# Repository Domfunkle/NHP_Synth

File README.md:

# NHP_Synth: ESP32 Dual DDS Synthesizer

This project implements a dual-channel Direct Digital Synthesis (DDS) signal generator on the ESP32 platform. It features:

- Two independent sine wave outputs (via DACs on GPIO25 and GPIO26)
- Precise square wave output (GPIO18) synchronized to DDS phase
- UART command interface for real-time control
- Phase, frequency, and amplitude control for each channel
- Odd harmonic mixing with amplitude and phase control per channel (total 8 simultaneous harmonics across both channels)
- External sync input (GPIO19, rising edge)
- High-resolution timer for accurate waveform generation

## Features
- **Frequency Range:** 20 Hz to 8 kHz (configurable)
- **Amplitude Ramping:** Smooth amplitude changes to prevent clicks
- **Phase Control:** Set phase offset for each channel
- **Harmonic Mixing:** Add odd harmonics (3rd, 5th, 7th, etc) to either channel, with amplitude and phase control. Up to a total of 8 harmonics can be active across both channels at once.
- **UART Commands:**
  - `wf[a|b]<freq>`: Set channel A or B frequency (Hz)
  - `wp[a|b]<deg>`: Set channel A or B phase (degrees, -180 to +180)
  - `wa[a|b]<ampl>`: Set channel A or B amplitude (0-100)
  - `wh[a|b]<order>,<pct>[,<phase>]`: Mix odd harmonic to channel A or B (e.g. `wha3,10` for 10% 3rd harmonic, or `wha7,20,-90` for 20% 7th harmonic at -90° phase)
  - `whcl[a|b]`: Clear all harmonics for channel A or B
  - `help`: Show help message

## Hardware Connections
- **DAC Channel A:** GPIO25
- **DAC Channel B:** GPIO26
- **Square Wave Output:** GPIO18
- **Sync Input:** GPIO19 (rising edge, with pulldown)

## Project Structure

```
NHP_Synth/
├── firmware/           # ESP32 firmware (ESP-IDF project)
│   ├── main/          # Main application source
│   ├── .devcontainer/ # ESP-IDF development container
│   └── .vscode/       # ESP32-specific VS Code settings
├── host/              # Python host control interface
│   ├── synth_control/ # Python control library
│   ├── examples/      # Usage examples
│   ├── .devcontainer/ # Python development container
│   └── .vscode/       # Python-specific VS Code settings
├── tools/             # Shared utilities and scripts
└── .vscode/           # Root workspace configuration
```

## Build & Flash

### Firmware (ESP32)
Navigate to the firmware directory and use ESP-IDF:

```bash
cd firmware
idf.py build
idf.py -p /dev/ttyUSB0 flash
```

Or use the convenient script for multiple devices:

```bash
./tools/flash_multiple.sh
```

## Host Control (Python)

A Python interface is provided for programmatic control:

```bash
cd host
python3 -m venv .venv
source .venv/bin/activate
pip install -r requirements.txt

# Run examples
python examples/basic_control.py
python examples/harmonic_sweep.py
```

## UART Usage
Connect to the ESP32 UART (default 115200 baud) and type commands as described above. Type `help` for a list of commands.

## Linux commands to test UART
```bash
# Generate a square wave on Channel A at 50Hz
printf "wha3,33\r" > /dev/ttyUSB1
printf "wha5,20\r" > /dev/ttyUSB1
printf "wha7,14\r" > /dev/ttyUSB1
printf "wha9,11\r" > /dev/ttyUSB1
printf "wha11,9\r" > /dev/ttyUSB1
printf "wha13,8\r" > /dev/ttyUSB1
printf "wha15,7\r" > /dev/ttyUSB1
printf "wha17,6\r" > /dev/ttyUSB1
```

```bash
# Clear all harmonics for Channel A and B
printf "whcla\r" > /dev/ttyUSB1
printf "whclb\r" > /dev/ttyUSB1
```

```bash
# Rolling harmonic phase for Channel A and B
ph=-180
while true; do
    printf "wha5,20,%d\n" "$ph" > /dev/ttyUSB1
    invph=$((ph * -1))
    printf "whb3,10,%d\n" "$invph" > /dev/ttyUSB1
    sleep 0.03
    ph=$((ph + 1))
    if [ "$ph" -gt 180 ]; then
        ph=-180
    fi
done
```

## Development

### VS Code Workspace
Open the multi-root workspace for unified development:
```bash
code .vscode/NHP_Synth.code-workspace
```

### DevContainers
Each component has its own development container:
- **Firmware**: ESP-IDF container with all tools
- **Host**: Python container with analysis libraries

### Tools
- `tools/flash_multiple.sh` - Flash firmware to multiple devices
- `tools/uart_test.py` - Test UART communication

## File Structure
- `firmware/main/main.c`: Main ESP32 application source
- `firmware/build/`: Build artifacts (ignored by git)
- `host/synth_control/`: Python control library
- `host/examples/`: Python usage examples
- `tools/`: Shared utilities and scripts
- `.gitignore`: Excludes build and config files from version control

## License
MIT License (or specify your license here)

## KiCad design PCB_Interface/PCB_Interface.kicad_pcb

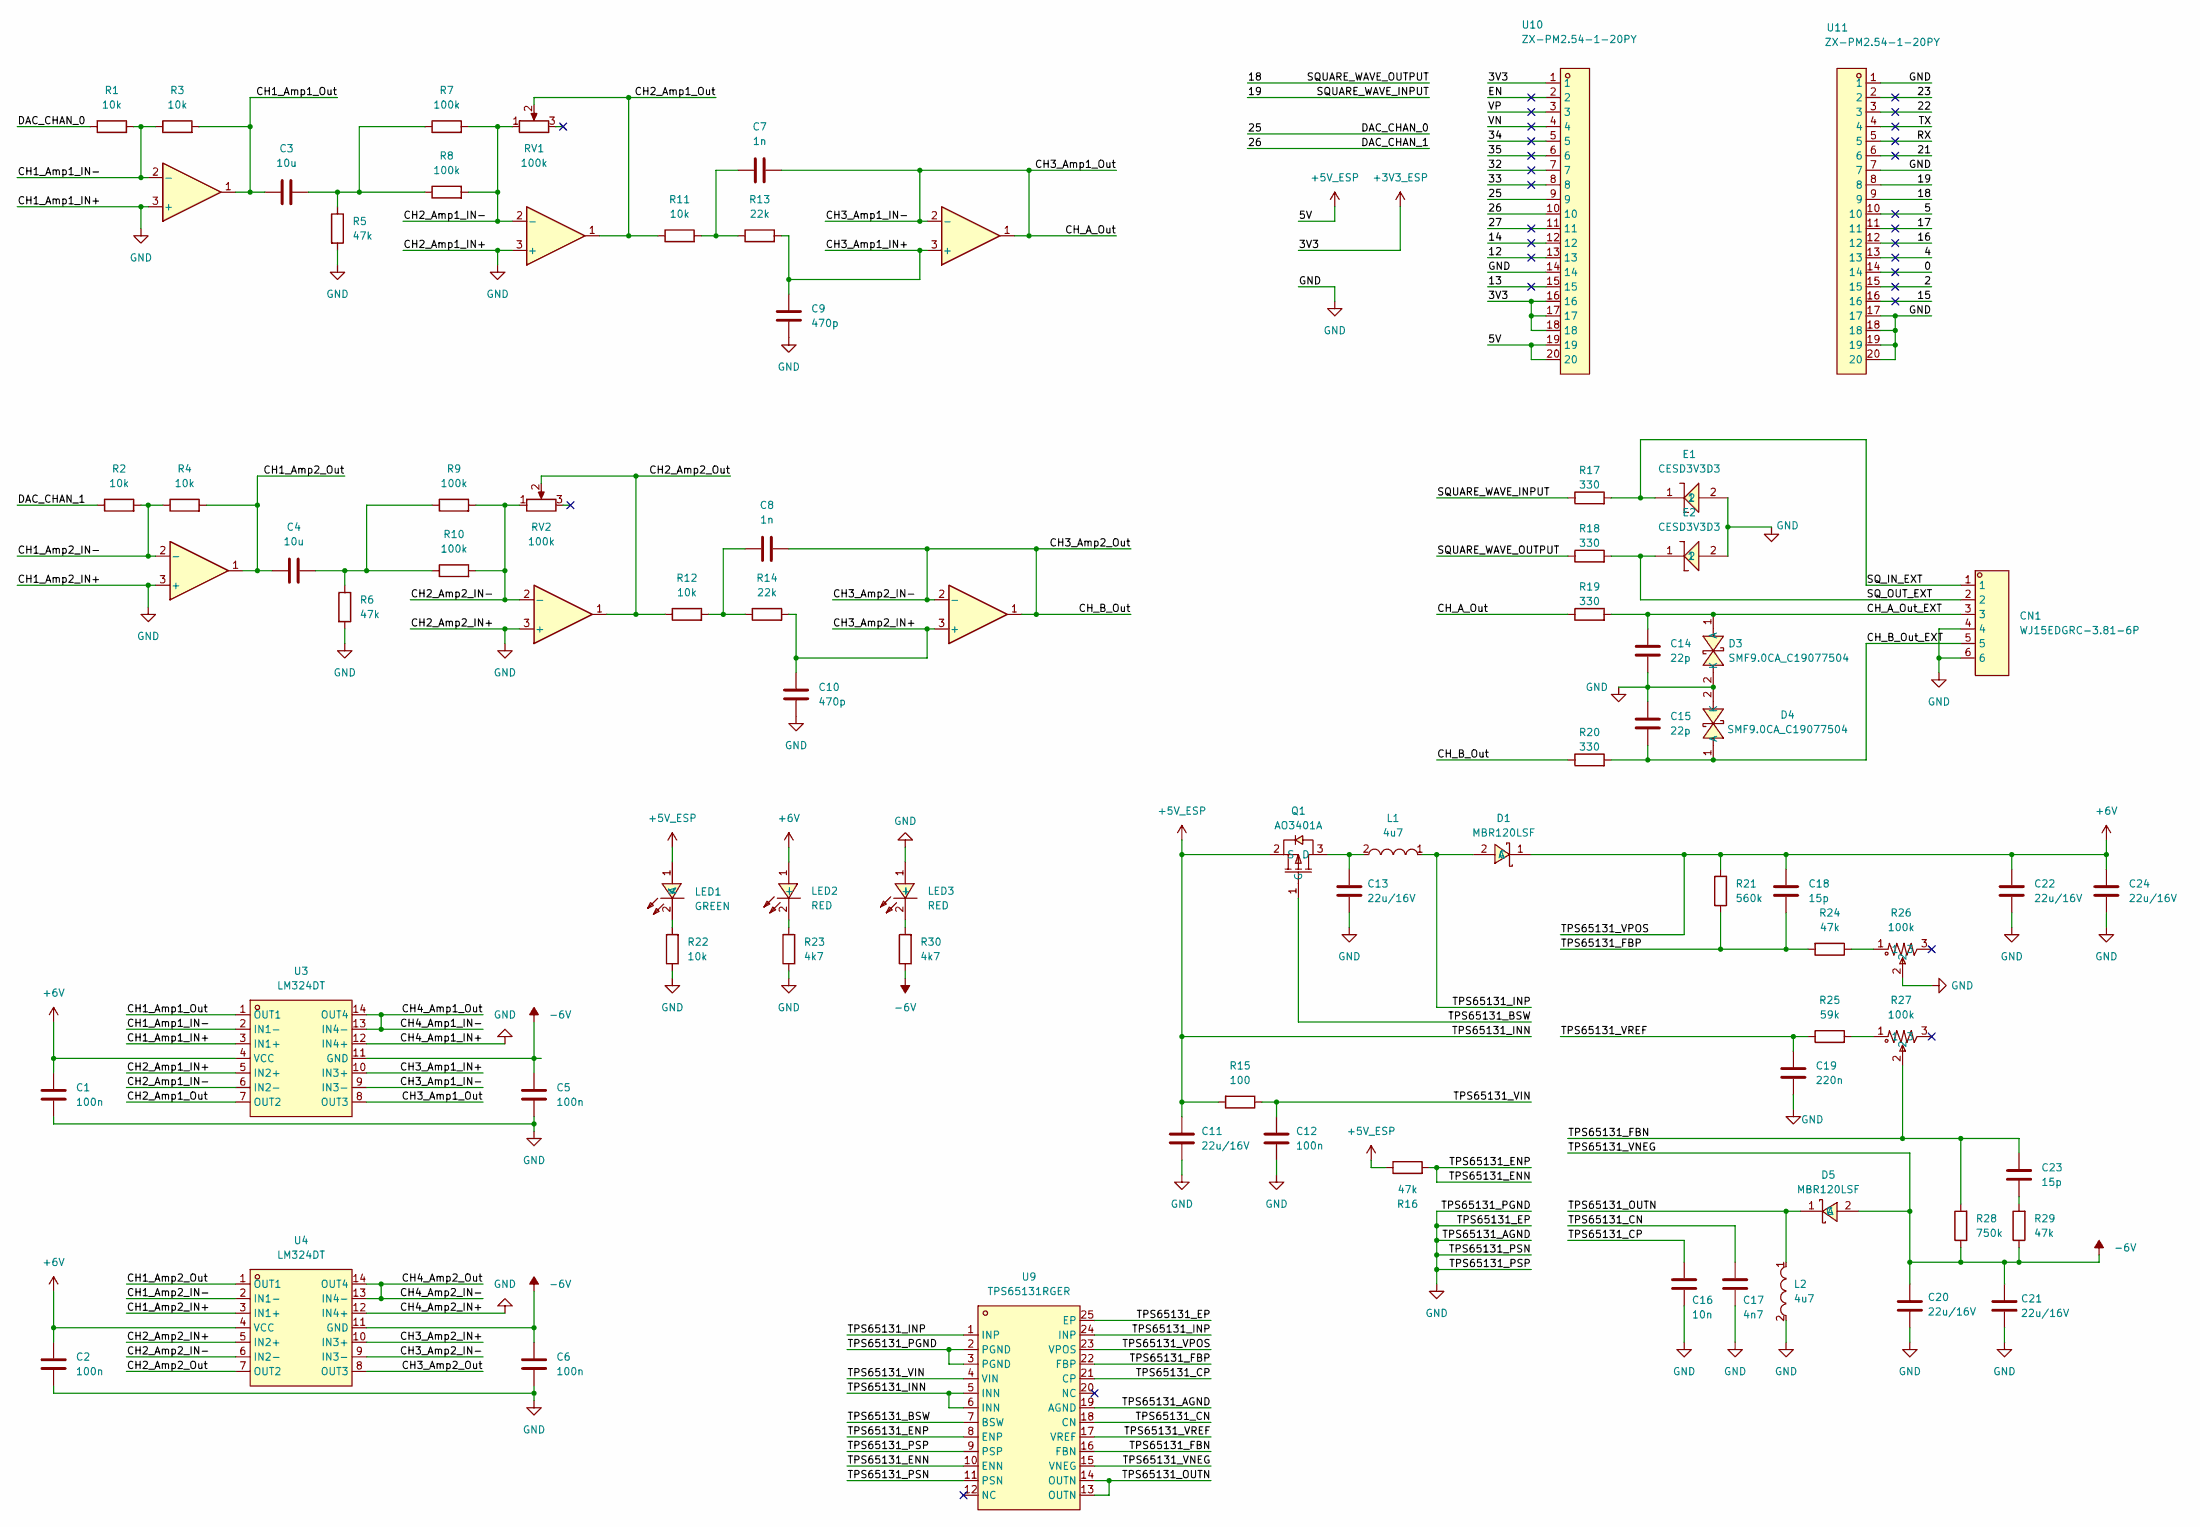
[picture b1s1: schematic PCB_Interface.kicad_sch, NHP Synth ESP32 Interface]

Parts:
C1, C2, C5, C6, C12: 100n; C_0603_1608Metric
C3, C4: 10u; C_0603_1608Metric
C7, C8: 1n; C_0603_1608Metric
C9, C10: 470p; C_0603_1608Metric
C11, C13, C20, C21, C22, C24: 22u/16V; C_0805_2012Metric
C14, C15: 22p; C_0603_1608Metric
C16: 10n; C_0603_1608Metric
C17: 4n7; C_0603_1608Metric
C18, C23: 15p; C_0603_1608Metric
C19: 220n; C_0603_1608Metric
CN1: WJ15EDGRC-3.81-6P; CONN-TH_WJ15EDGRC-3.81-6P; LCSC Part C7246
D1, D5: MBR120LSF; SOD-123_L2.8-W1.8-LS3.7-RD; LCSC Part C130880
D3, D4: SMF9.0CA_C19077504; SOD-123FL_L2.7-W1.8-LS3.8-BI; LCSC Part C19077504
E1, E2: CESD3V3D3; SOD-323_L1.8-W1.3-LS2.5-RD; LCSC Part C38388
L1, L2: 4u7; IND-SMD_L5.4-W5.2_FXL0530; LCSC Part C177246
LED1: GREEN; LED0805-R-RD; LCSC Part C2297
LED2, LED3: RED; LED0805-R-RD; LCSC Part C84256
Q1: AO3401A; SOT-23_L2.9-W1.3-P1.90-LS2.4-BR; LCSC Part C15127
R1, R2, R3, R4, R11, R12, R22: 10k; R_0603_1608Metric
R5, R6, R16, R24, R29: 47k; R_0603_1608Metric
R7, R8, R9, R10: 100k; R_0603_1608Metric
R13, R14: 22k; R_0603_1608Metric
R15: 100; R_0603_1608Metric
R17, R18, R19, R20: 330; R_0603_1608Metric
R21: 560k; R_0603_1608Metric
R23, R30: 4k7; R_0603_1608Metric
R25: 59k; R_0603_1608Metric
R26, R27: 100k; RES-ADJ-SMD_TC33X-2-104E; LCSC Part C719186
R28: 750k; R_0603_1608Metric
RV1, RV2: 100k; RES-ADJ-TH_3296P; LCSC Part C780112
U1, U2, U5, U6, U7, U8: LM324
U3, U4: LM324DT; SOIC-14_L8.7-W3.9-P1.27-LS6.0-BL; LCSC Part C71035
U9: TPS65131RGER; QFN-24_L4.0-W4.0-P0.50-TL-EP2.6; LCSC Part C87663
U10, U11: ZX-PM2.54-1-20PY; HDR-TH_20P-P2.54-V-F; LCSC Part C7499336

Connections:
+3V3_ESP: U10.1, U10.16, U10.17, U10.18
+5V_ESP: C11.1, LED1.1 (A), Q1.2 (S), R15.2, R16.1, U9.5 (INN), U9.6 (INN), U10.19, U10.20
+6V: C1.2, C2.2, C18.1, C22.1, C24.1, D1.1 (C), LED2.1 (+), R21.2, U3.4 (VCC), U4.4 (VCC), U9.23 (VPOS)
-6V: C5.2, C6.2, C20.1, C21.1, D5.2 (A), R28.1, R29.1, R30.1, U3.11 (GND), U4.11 (GND), U9.15 (VNEG)
/0: U11.14
/2: U11.15
/4: U11.13
/5: U11.10
/12: U10.13
/13: U10.15
/14: U10.12
/15: U11.16
/16: U11.12
/17: U11.11
/18: R18.1, U11.9
/19: R17.1, U11.8
/21: U11.6
/22: U11.3
/23: U11.2
/25: R1.1, U10.9
/26: R2.1, U10.10
/27: U10.11
/32: U10.7
/33: U10.8
/34: U10.5
/35: U10.6
/CH1_Amp1_IN-: R1.2, R3.1, U1.2 (-), U3.2 (IN1-)
/CH1_Amp1_Out: C3.1, R3.2, U1.1, U3.1 (OUT1)
/CH1_Amp2_IN-: R2.2, R4.1, U2.2 (-), U4.2 (IN1-)
/CH1_Amp2_Out: C4.1, R4.2, U2.1, U4.1 (OUT1)
/CH2_Amp1_IN-: R7.2, R8.2, RV1.1, U3.6 (IN2-), U5.2 (-)
/CH2_Amp1_Out: R11.1, RV1.2, U3.7 (OUT2), U5.1
/CH2_Amp2_IN-: R9.2, R10.2, RV2.1, U4.6 (IN2-), U6.2 (-)
/CH2_Amp2_Out: R12.1, RV2.2, U4.7 (OUT2), U6.1
/CH3_Amp1_IN+: C9.2, R13.2, U3.10 (IN3+), U7.3 (+)
/CH3_Amp1_IN-: C7.2, R19.1, U3.8 (OUT3), U3.9 (IN3-), U7.1, U7.2 (-)
/CH3_Amp2_IN+: C10.2, R14.2, U4.10 (IN3+), U8.3 (+)
/CH3_Amp2_IN-: C8.2, R20.1, U4.8 (OUT3), U4.9 (IN3-), U8.1, U8.2 (-)
/CH4_Amp1_IN-: U3.13 (IN4-), U3.14 (OUT4)
/CH4_Amp2_IN-: U4.13 (IN4-), U4.14 (OUT4)
/CH_A_Out_EXT: C14.1, CN1.3, D3.1 (A), R19.2
/CH_B_Out_EXT: C15.2, CN1.5, D4.1 (A), R20.2
/EN: U10.2
/RX: U11.5
/SQ_IN_EXT: CN1.1, E1.1, R17.2
/SQ_OUT_EXT: CN1.2, E2.1, R18.2
/TPS65131_BSW: Q1.1 (G), U9.7 (BSW)
/TPS65131_CN: C17.1, U9.18 (CN)
/TPS65131_CP: C16.1, U9.21 (CP)
/TPS65131_ENN: R16.2, U9.8 (ENP), U9.10 (ENN)
/TPS65131_FBN: C23.1, R27.2, R28.2, U9.16 (FBN)
/TPS65131_FBP: C18.2, R21.1, R24.2, U9.22 (FBP)
/TPS65131_INP: D1.2 (A), L1.1, U9.1 (INP), U9.24 (INP)
/TPS65131_OUTN: D5.1 (C), L2.1, U9.13 (OUTN), U9.14 (OUTN)
/TPS65131_VIN: C12.1, R15.1, U9.4 (VIN)
/TPS65131_VREF: C19.1, R25.1, U9.17 (VREF)
/TX: U11.4
/VN: U10.4
/VP: U10.3
GND: C1.1, C2.1, C5.1, C6.1, C9.1, C10.1, C11.2, C12.2, C13.2, C14.2, C15.1, C16.2, C17.2, C19.2, C20.2, C21.2, C22.2, C24.2, CN1.4, CN1.6, D3.2 (K), D4.2 (K), E1.2, E2.2, L2.2, LED3.1 (+), R5.2, R6.2, R22.1, R23.1, R26.2, U1.3 (+), U2.3 (+), U3.3 (IN1+), U3.5 (IN2+), U3.12 (IN4+), U4.3 (IN1+), U4.5 (IN2+), U4.12 (IN4+), U5.3 (+), U6.3 (+), U9.2 (PGND), U9.3 (PGND), U9.9 (PSP), U9.11 (PSN), U9.19 (AGND), U9.25 (EP), U10.14, U11.1, U11.7, U11.17, U11.18, U11.19, U11.20
unnamed: C3.2, R5.1, R7.1, R8.1
unnamed: C4.2, R6.1, R9.1, R10.1
unnamed: C7.1, R11.2, R13.1
unnamed: C8.1, R12.2, R14.1
unnamed: C23.2, R29.2
unnamed: LED1.2 (K), R22.2
unnamed: LED2.2 (-), R23.2
unnamed: LED3.2 (-), R30.2
unnamed: C13.1, L1.2, Q1.3 (D)
unnamed: R24.1, R26.1
unnamed: R25.2, R27.1

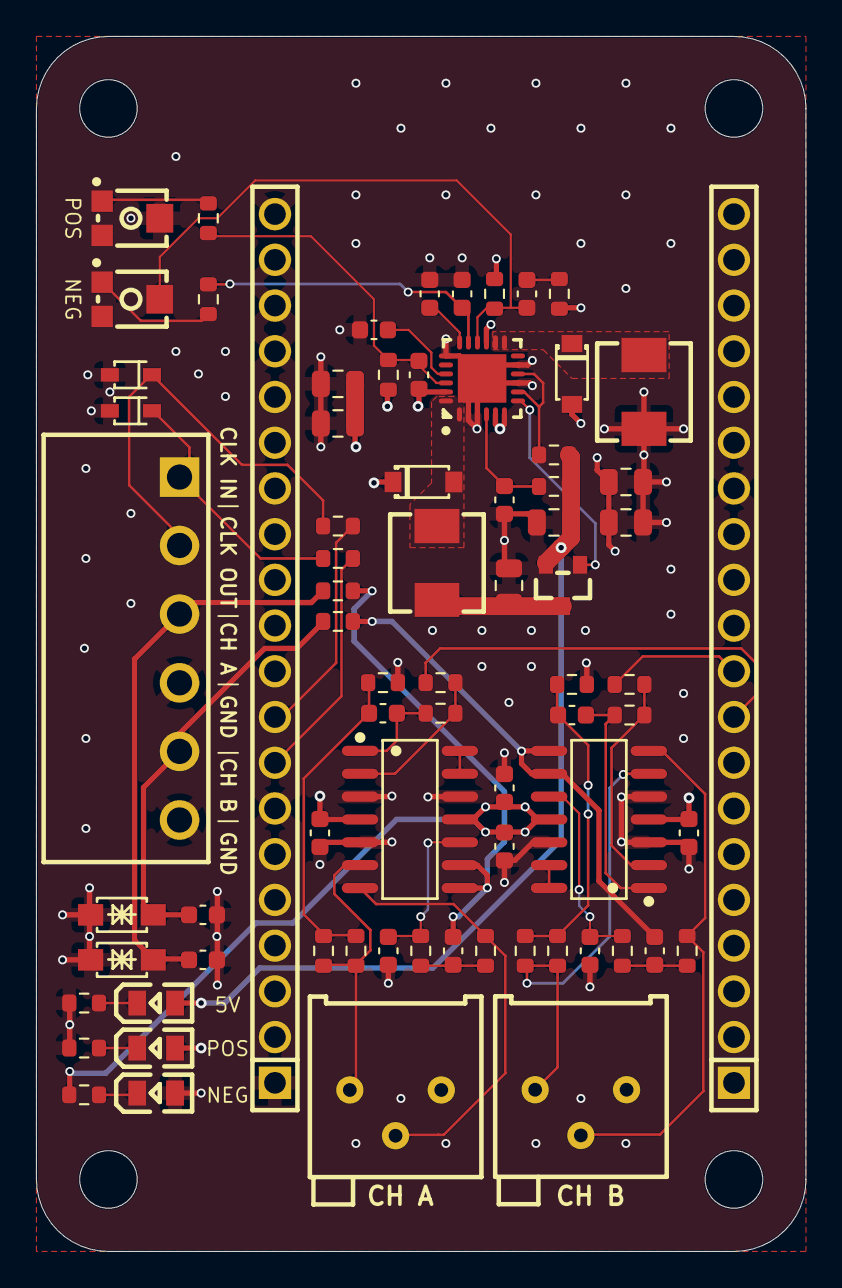
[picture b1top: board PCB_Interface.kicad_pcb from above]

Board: 4 copper layers, 42.8 x 67.5 mm, 74 parts (0 on the bottom side), 48 nets.

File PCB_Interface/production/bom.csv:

Designator,Footprint,Quantity,Value,LCSC Part #
"C1, C12, C2, C5, C6",0603,5,100n,
"C10, C9",0603,2,470p,
"C11, C13, C20, C21, C22, C24",0805,6,22u/16V,
"C14, C15",0603,2,22p,
C16,0603,1,10n,
C17,0603,1,4n7,
"C18, C23",0603,2,15p,
C19,0603,1,220n,
"C3, C4",0603,2,10u,
"C7, C8",0603,2,1n,
CN1,CONN-TH_WJ15EDGRC-3.81-6P,1,WJ15EDGRC-3.81-6P,C7246
"D1, D5",SOD-123_L2.8-W1.8-LS3.7-RD,2,MBR120LSF,C130880
"D3, D4",SOD-123FL_L2.7-W1.8-LS3.8-BI,2,SMF9.0CA_C19077504,C19077504
"E1, E2",SOD-323_L1.8-W1.3-LS2.5-RD,2,CESD3V3D3,C38388
"L1, L2",IND-SMD_L5.4-W5.2_FXL0530,2,4u7,C177246
LED1,LED0805-R-RD,1,GREEN,C2297
"LED2, LED3",LED0805-R-RD,2,RED,C84256
Q1,SOT-23_L2.9-W1.3-P1.90-LS2.4-BR,1,AO3401A,C15127
"R1, R11, R12, R2, R22, R3, R4",0603,7,10k,
"R10, R7, R8, R9",0603,4,100k,
"R13, R14",0603,2,22k,
R15,0603,1,100,
"R16, R24, R29, R5, R6",0603,5,47k,
"R17, R18, R19, R20",0603,4,330,
R21,0603,1,560k,
"R23, R30",0603,2,4k7,
R25,0603,1,59k,
"R26, R27",RES-ADJ-SMD_TC33X-2-104E,2,100k,C719186
R28,0603,1,750k,
"RV1, RV2",RES-ADJ-TH_3296P,2,100k,C780112
"U10, U11",HDR-TH_20P-P2.54-V-F,2,ZX-PM2.54-1-20PY,C7499336
"U3, U4",SOIC-14_L8.7-W3.9-P1.27-LS6.0-BL,2,LM324DT,C71035
U9,QFN-24_L4.0-W4.0-P0.50-TL-EP2.6,1,TPS65131RGER,C87663

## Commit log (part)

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2025-07-08 update gitignore to include sdkconfig and archive files
2025-07-08 fix: correct command syntax for flashing multiple devices in README
2025-07-08 feat: add harmonic mixing functionality and update cosine table generation
2025-07-09 updated UART to unified command style (e.g. wh[a|b] instead of separate wha whb)
2025-07-10 refactor: update harmonic mixing implementation and optimize cosine table generation
2025-07-10 refactor: optimize waveform generation and harmonics handling
2025-07-11 comment out debug logging
2025-07-11 comment out logging
2025-07-11 enhance harmonic handling
2025-07-11 maximum harmonics limit global rather than per channel
2025-07-22 Add NHP_Synth control interface and examples
    - Implemented a Python interface for controlling the ESP32 NHP_Synth dual-channel DDS synthesizer.
    - Created a development container configuration for easy setup.
    - Added README documentation with installation instructions and usage examples.
    - Developed example scripts for basic control and harmonic demonstrations.
    - Introduced a main control program using a rotary encoder for amplitude adjustments.
    - Included utilities for waveform generation and harmonic synthesis.
2025-07-22 Enhance synthesizer connection handling and amplitude control for multiple devices
2025-07-22 Refactor main control logic for multi-encoder functionality and improve error handling for synthesizer connections
2025-07-22 Improve square wave generation by using channel A frequency for period calculation and adding dynamic recalculation on frequency change
2025-07-23 Reset target amplitude values to zero and comment out unused timer control functions
2025-07-23 Update flash_multiple.sh to build firmware before flashing multiple ESP32 devices
2025-07-23 Remove normalization and apply amplitude scaling directly
2025-07-24 Update ESP-IDF version to 5.4.2 in sdkconfig
2025-07-24 Fix firmware directory path in flash_multiple.sh script
2025-07-24 Update frequency adjustment to allow 0.1Hz changes for all synthesizers
2025-07-24 Update flash_multiple.sh to dynamically find serial devices and resolve symlinks
2025-07-24 Optimize initialization, add color console output, and refactor code architecture
    - Speed up I2C encoder init with concurrent processing (50-65% faster)
    - Add comprehensive ANSI color-coded console output with timing metrics
    - Implement cached I2C scanning and reduced retry delays
    - Refactor into modular functions: initialize_system(), handle_encoder_buttons(), handle_encoder_rotation()
    - Add detailed initialization progress tracking and hardware status reporting
    - Improve USB device scanning with priority-based filtering
2025-07-24 Multi-encoder control: default all-synth/channel mode, button for individual selection
    - Changed default behavior: all encoders (amplitude, frequency, phase, harmonics) affect all synths/channels simultaneously
    - Button press on encoder switches to individual synth/channel selection mode for that encoder
    - Cycling through individual synths/channels returns to "all" mode before wrapping
    - Added 60-second timeout: after inactivity, encoder reverts to "all" mode
    - Updated phase encoder: in "all" mode, only adjusts channel B on all synths (not both channels)
    - Updated reset logic and messages to reflect new phase behavior
2025-07-24 extend phase adjust to +=360 deg
2025-07-25 Add defaults and state management for synthesizers
2025-07-25 Refactor synth defaults to include separate frequency and phase parameters for each channel
2025-07-25 Add 3rd and 5th harmonics for both channels with appropriate phase adjustments
2025-07-25 Harmonics handling uses lists of dictionaries for amplitude and phase, for both channels.
2025-07-25 Initialize system with default synth state if not present
2025-07-25 Add SynthDiscovery class for USB device discovery and refactor main.py to utilize it; introduce Colors utility class for console output
2025-07-25 Refactor synthesizer control library
    - Renamed `uart_interface` to `synth_interface` and updated imports accordingly.
    - Added `synth_interface.py` to provide a UART interface for controlling the NHP_Synth synthesizer.
    - Introduced `system_initializer.py` to handle full system initialization, including I2C rotary encoder setup and synthesizer connections.
    - Updated `waveform_generator.py` to use the new `synth_interface`.
    - Enhanced the initialization process with detailed logging and error handling for better diagnostics.
2025-07-25 Remove init_single_encoder function to streamline encoder initialization process
2025-07-25 Add EncoderManager for handling encoder interactions and create physical test checklist
    - Introduced EncoderManager class to manage encoder button presses and rotations, including hold detection and state management for amplitude, frequency, phase, and harmonics.
    - Implemented functionality for resetting values, switching between individual and all synth modes, and handling harmonics updates.
    - Added a new physical test checklist to ensure hardware/software integration after code changes, covering various tests such as encoder detection, button presses, LED feedback, and error handling.
2025-07-25 cleanup
2025-07-25 converted print to common logging function
2025-07-25 Save synth state after resetting to defaults
2025-07-25 Update to .venv and add add separate test routine
2025-07-25 Remove synth_state.json and update .gitignore to exclude it
2025-07-26 Change UART command task to run on core 1
    esp_timer always runs on core 0
2025-07-26 Increase UART command task stack size and adjust amplitude ramp step
2025-07-26 Enhance SynthInterface and SystemInitializer with ID support; add state retrieval methods in test routine
2025-07-28 Complete overhaul of code structure and functionality
    - New classes and methods for Encoder management
    - Improved state management with deep copies
    - Enhanced Flask-SocketIO integration for real-time updates
    - Added threading for background tasks
    - Web dashboard using bootstrap and chartJS
    - Updated HTML and JavaScript for better user experienc
2025-07-28 Add increment/decrement handlers for voltage, current, phase, and frequency; enhance UI controls
2025-07-28 Share selection mode state with EncoderManager and update web server to emit selection mode in synth state
2025-07-28 Implement selection mode timeout handling and reset inactivity timer in EncoderManager
2025-07-28 Add selection mode tracking to synth state emission
2025-07-28 offcanvas at bottom for parameter control
2025-07-28 indenting
2025-07-28 moved components to new js file
2025-07-28 moved state management to new js file
2025-07-28 moved handler logic to separate file
2025-07-29 added bootstrap icons
2025-07-29 default phase values from -120 to 240
2025-07-29 new functions for resetting to defaults
2025-07-29 added frequency handling in offcanvas
2025-07-29 enhanced UI for voltage/current offcanvas. in process of creating harmonic offcanvas
2025-07-29 commands from client now use websocket messages instead of POST
2025-07-30 enhanced offcanvas adjustment for combined waveform
2025-07-30 harmonic order control from UI
2025-07-30 fixed issue where defaults overwritten by current state
2025-07-30 update harmonic setting methods to use structured data
2025-07-30 refactor: standardize AppState property naming from 'synthstate' to 'synthState'
2025-07-31 clears old harmonics when order changed, when defaults are set, and when initialized
2025-07-31 highlighed selection mode functional
2025-07-31 full harmonic adjustment functionality
2025-07-31 fixed up adjustment value with set selection
2025-07-31 power factor included in accordion header
2025-07-31 fixed issue where harmonic dial selection affected all synths instead of one.
2025-07-31 refactor. using PF and THDi in accordion headers
2025-07-31 refactor: move SynthWaveformChart to charts.js for better modularity
2025-07-31 Refactor: Move DPF, THD, truePF, and getGlobalFrequencyHz functions to utils.js
2025-07-31 refactor global windows and exports, general restructuring
2025-07-31 move selection logic to a dedicated module and clean up component exports
2025-07-31 defaults are 0 voltage harmonics, 4x current harmonics
2025-07-31 fixed mutable defaults being updated unintentionally
2025-07-31 harmonic property reset functionality enabled for ui
2025-08-01 negative phases allowed with rollover at +-180
2025-08-01 enabled phase rollover at +-180 for encoder rotation
2025-08-01 fixed individual phase wrapping of +-180
2025-08-01 separated out custom css
2025-08-01 removed accordion, replaced with full-widtch cards
2025-08-02 fixed up formatting of offcanvas with harmonic tables
2025-08-02 fixed harmonic increment, voltage range to 250, global max V and I
2025-08-02 fixed defaults
2025-08-02 fixed state management issues with defaults overwriting
2025-08-03 refactor waveform chart functions and update UI components for single and three-phase rendering
2025-08-03 nav bar placeholder, vertical lines to separate card cols, horizontal zero-crossing in charts
2025-08-03 feat: Add enable/disable functionality for synth channels
    - Updated firmware to include per-channel output enable/disable states and ramping.
    - Modified UART command handling to support reading and writing output enable states.
    - Enhanced host defaults to initialize enabled states for channels.
    - Implemented socket communication for enabling/disabling synth channels from the dashboard.
    - Added UI components for toggling channel enable states with visual feedback.
    - Updated command processing to handle new enable/disable commands.
2025-08-04 charts rendered around x=0
2025-08-04 better LED init
2025-08-04 feat: Add voltage, current, and horizontal scaling functionality for three-phase waveform chart
2025-08-04 Enhance three-phase waveform chart with phase visibility controls and state management
2025-08-04 feat: Implement settings management and enhance synth handlers
    - Added settings management endpoints in web_server.py for getting, saving, and resetting settings.
    - Introduced a settings.js module for handling settings initialization, updates, and UI interactions.
    - Updated synthHandlers.js to utilize dynamic max voltage and current settings from settings.js.
    - Enhanced error handling with a centralized errorHandler.js module.
    - Created app.js as the main application controller, managing socket connections and rendering.
    - Added debounce and throttle utilities in utils.js for performance optimization.
2025-08-04 auto-restart and kiosk mode scripts
2025-08-10 Add initial configuration files for PCB interface
2025-12-04 fix: Minimize glitches in DDS output by resetting accumulator at waveform peak
2025-12-04 feat: Enhance logging and readiness checks in kiosk and main scripts
2025-12-04 feat: Implement service status and logs management with auto-refresh in dashboard
2025-12-04 fix: Adjust logs view height and remove auto-refresh note for clarity
2025-12-05 fix: Disable Bootstrap hover effects for buttons, nav links, and list items for consistency
2025-12-10 fix: Enhance cleanup function to handle background processes and FIFO files
2025-12-10 fix: Update .gitignore to include additional log and autostart pipe files
2025-12-10 feat: Add desktop entry for NHP Synth application launcher
2026-02-13 Update PCB production outputs
2026-04-30 host now maintains an authoritative shared state by polling the physical synths and reconciling state continuously, so all WebUI clients should converge to the same values.
2026-05-01 feat(command-queue): refactor harmonic update logic into a separate function for better maintainability
2026-05-05 feat(synth-poller): enhance polling logic to track update and failure counts feat(system-initializer): improve synth reconnection logic and state synchronization refactor(synth-state): include synth_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
